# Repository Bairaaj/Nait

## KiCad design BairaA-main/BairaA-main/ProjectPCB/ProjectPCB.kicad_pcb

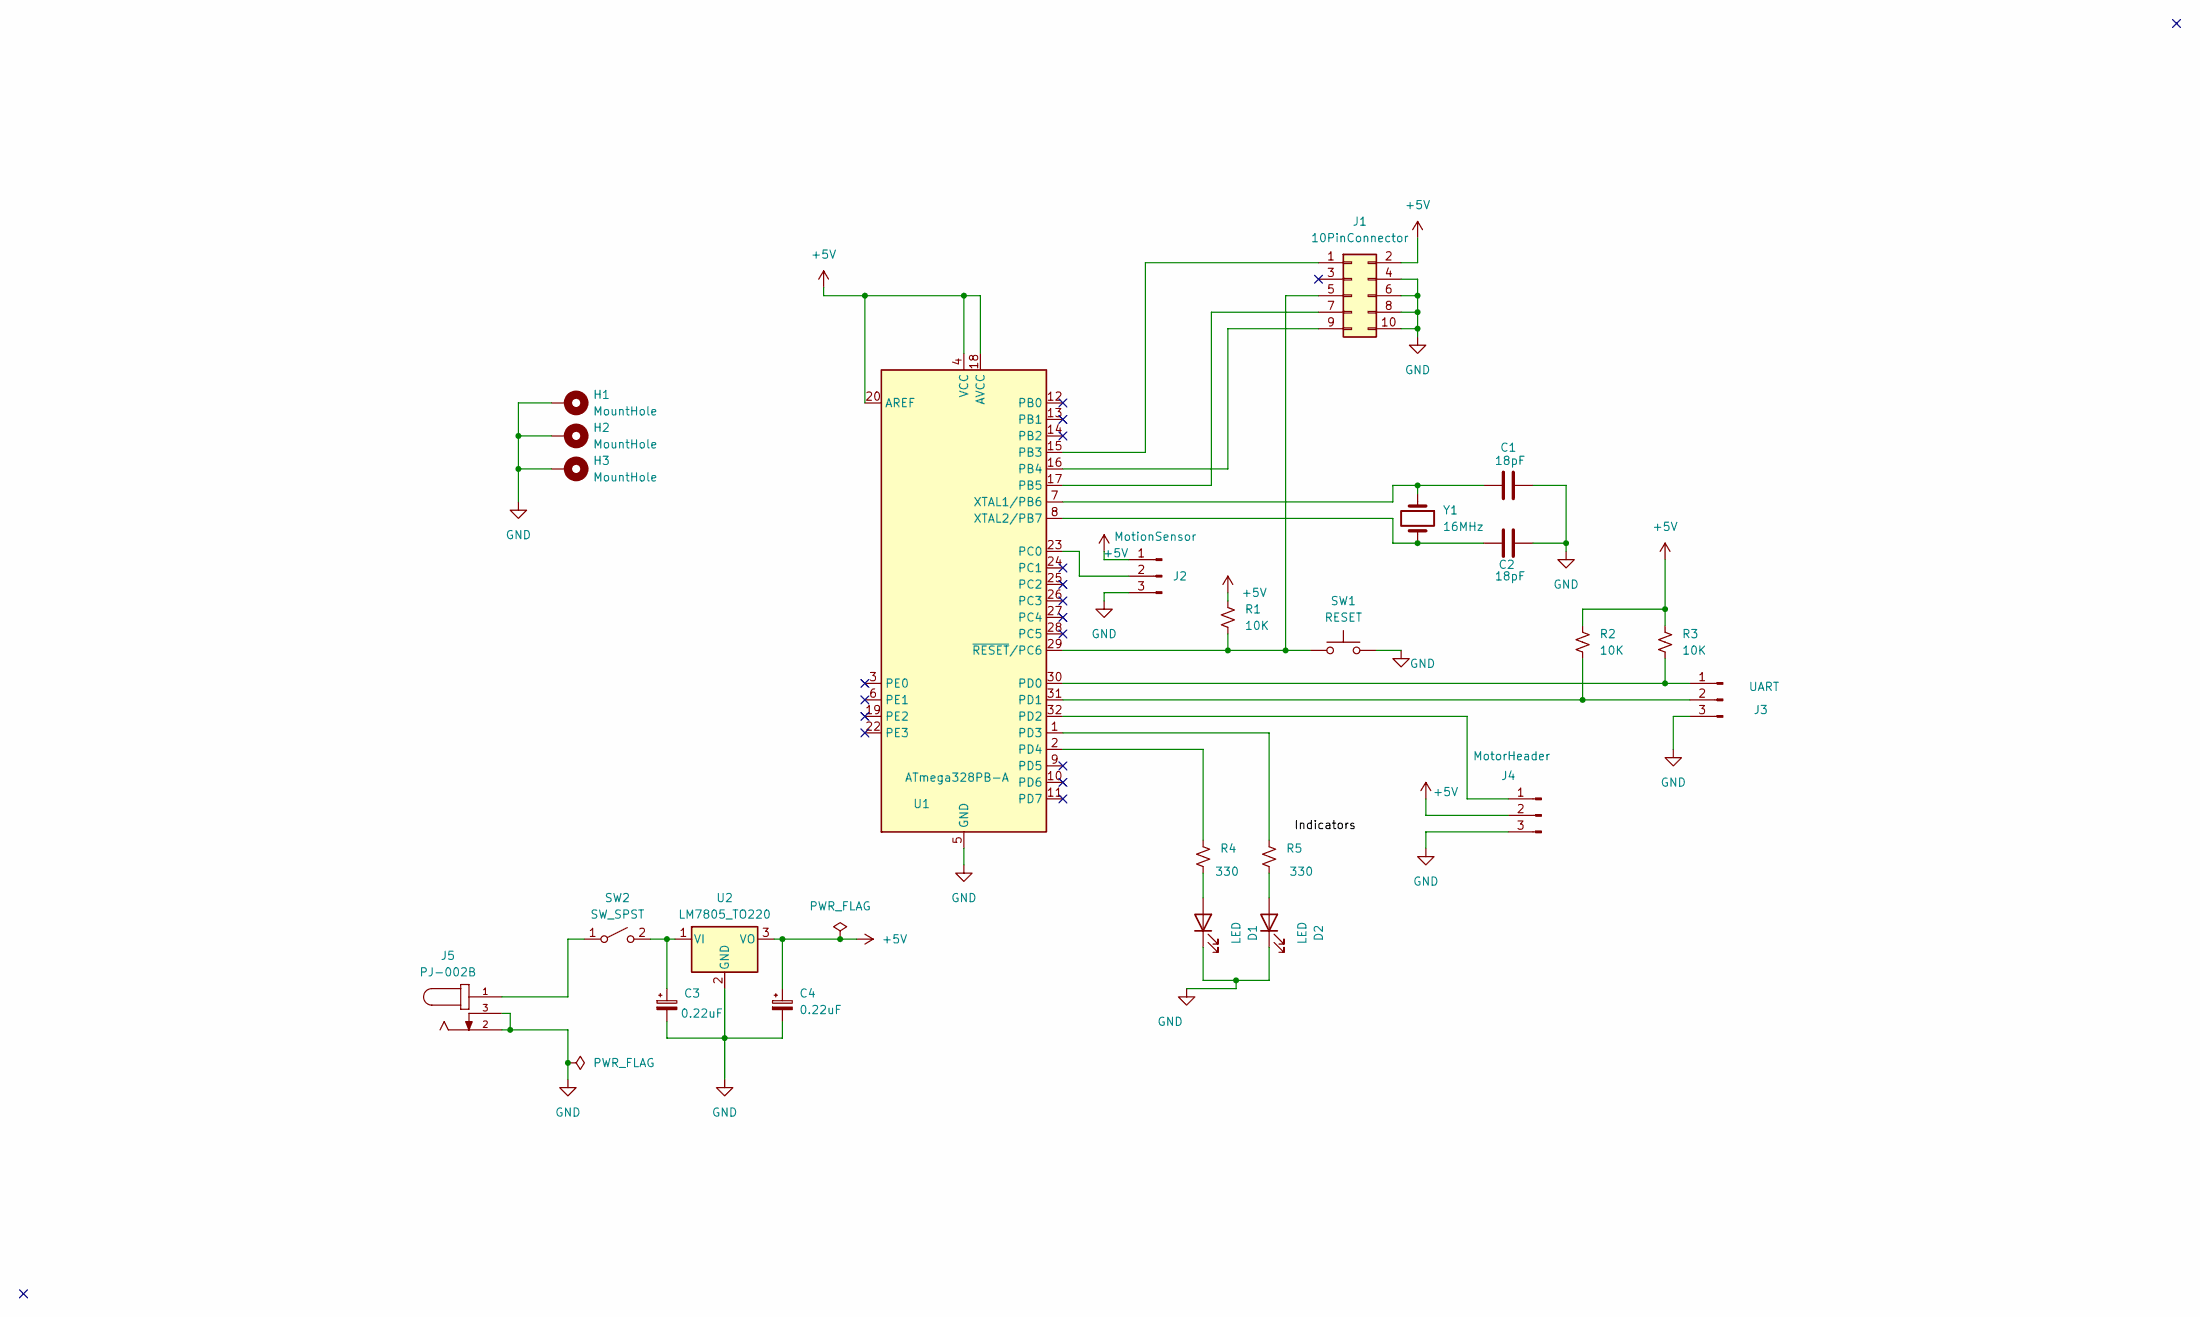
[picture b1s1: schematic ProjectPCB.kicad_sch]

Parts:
C1, C2: 18pF; C_0805_2012Metric
C3, C4: 0.22uF; C_0805_2012Metric
D1, D2: LED; LED_D3.0mm
H1, H2, H3: MountHole; MountingHole_2.2mm_M2_DIN965_Pad
J1: 10PinConnector; PinHeader_2x05_P2.54mm_Vertical
J2: MotionSensor; PinHeader_1x03_P2.54mm_Vertical
J3: UART; PinHeader_1x03_P2.54mm_Vertical
J4: MotorHeader; PinHeader_1x03_P2.54mm_Vertical
J5: PJ-002B; CUI_PJ-002B
R1, R2, R3: 10K; R_0805_2012Metric
R4, R5: 330; R_0805_2012Metric
SW1: RESET; SW_PUSH_1P1T_6x3.5mm_H4.3_APEM_MJTP1243
SW2: SW_SPST; SW_DIP_SPSTx01_Slide_6.7x4.1mm_W7.62mm_P2.54mm_LowProfile
U1: ATmega328PB-A; TQFP-32_7x7mm_P0.8mm
U2: LM7805_TO220; TO-220-3_Vertical
Y1: 16MHz; Crystal_SMD_HC49-SD

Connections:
+5V: C4.1, J1.2, J2.1, J4.2, R1.1, R2.2, R3.2, U1.4 (VCC), U1.18 (AVCC), U1.20 (AREF), U2.3 (VO)
GND: C1.2, C2.2, C3.2, C4.2, D1.1 (K), D2.1 (K), H1.1, H2.1, H3.1, J1.4, J1.6, J1.8, J1.10, J2.3, J3.3, J4.3, J5.2, J5.3, SW1.2, U1.5 (GND), U1.21 (GND), U2.2 (GND)
unnamed: D1.2 (A), R4.1
unnamed: D2.2 (A), R5.1
unnamed: J1.1, U1.15 (PB3)
unnamed: J1.5, R1.2, SW1.1, U1.29 (~RESET/PC6)
unnamed: J1.7, U1.17 (PB5)
unnamed: J1.9, U1.16 (PB4)
unnamed: J2.2, U1.23 (PC0)
unnamed: J3.1, R3.1, U1.30 (PD0)
unnamed: J3.2, R2.1, U1.31 (PD1)
unnamed: J4.1, U1.32 (PD2)
unnamed: J5.1, SW2.1 (A)
unnamed: C3.1, SW2.2 (B), U2.1 (VI)
unnamed: R5.2, U1.1 (PD3)
unnamed: R4.2, U1.2 (PD4)
unnamed: C1.1, U1.7 (XTAL1/PB6), Y1.1
unnamed: C2.1, U1.8 (XTAL2/PB7), Y1.2

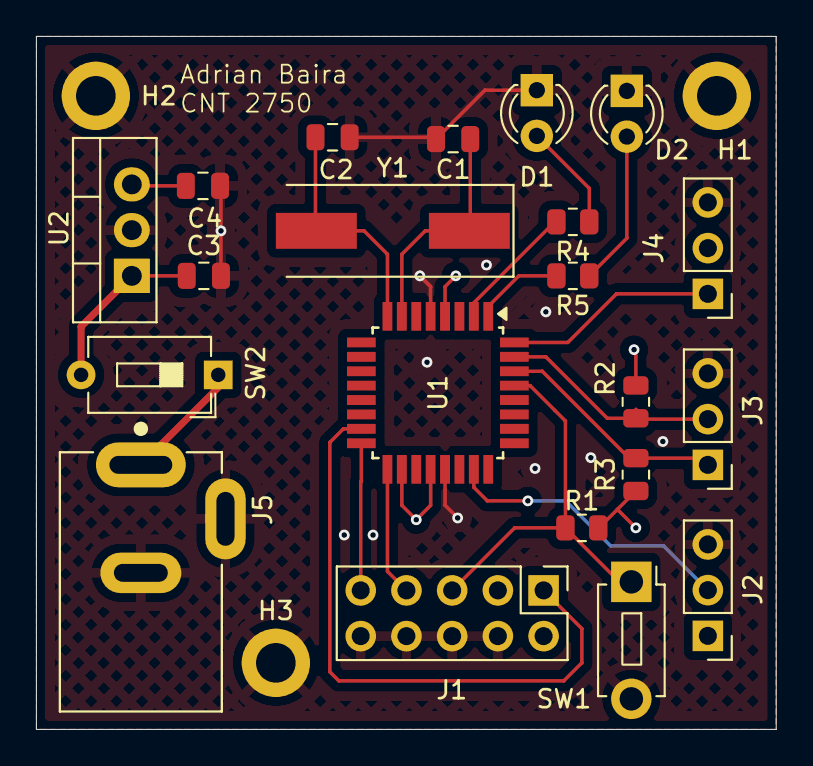
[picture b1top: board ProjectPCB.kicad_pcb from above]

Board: 4 copper layers, 41.1 x 38.5 mm, 24 parts (0 on the bottom side), 18 nets.

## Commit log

2025-04-28 All school stuff
